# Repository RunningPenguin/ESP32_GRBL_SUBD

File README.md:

# ESP32_GRBL_SUBD

ESP32 GRBL adapter to SUB-D25

adapter to use the [ESP32 GRBL port](https://github.com/bdring/Grbl_Esp32) with
usual CNC machines, which are controlled via LPT (SUB-D25)

## PCB
PCBs [version 0.9.2](https://github.com/RunningPenguin/ESP32_GRBL_SUBD/tree/v0.9.2) could be
purchased using the gerber files contained in "gerbers/ESP32_GRBL_SUBD.zip" at JLCPCB

### TOP side

### BOT side

### received PCBs

### assembled PCB

### attached PCB

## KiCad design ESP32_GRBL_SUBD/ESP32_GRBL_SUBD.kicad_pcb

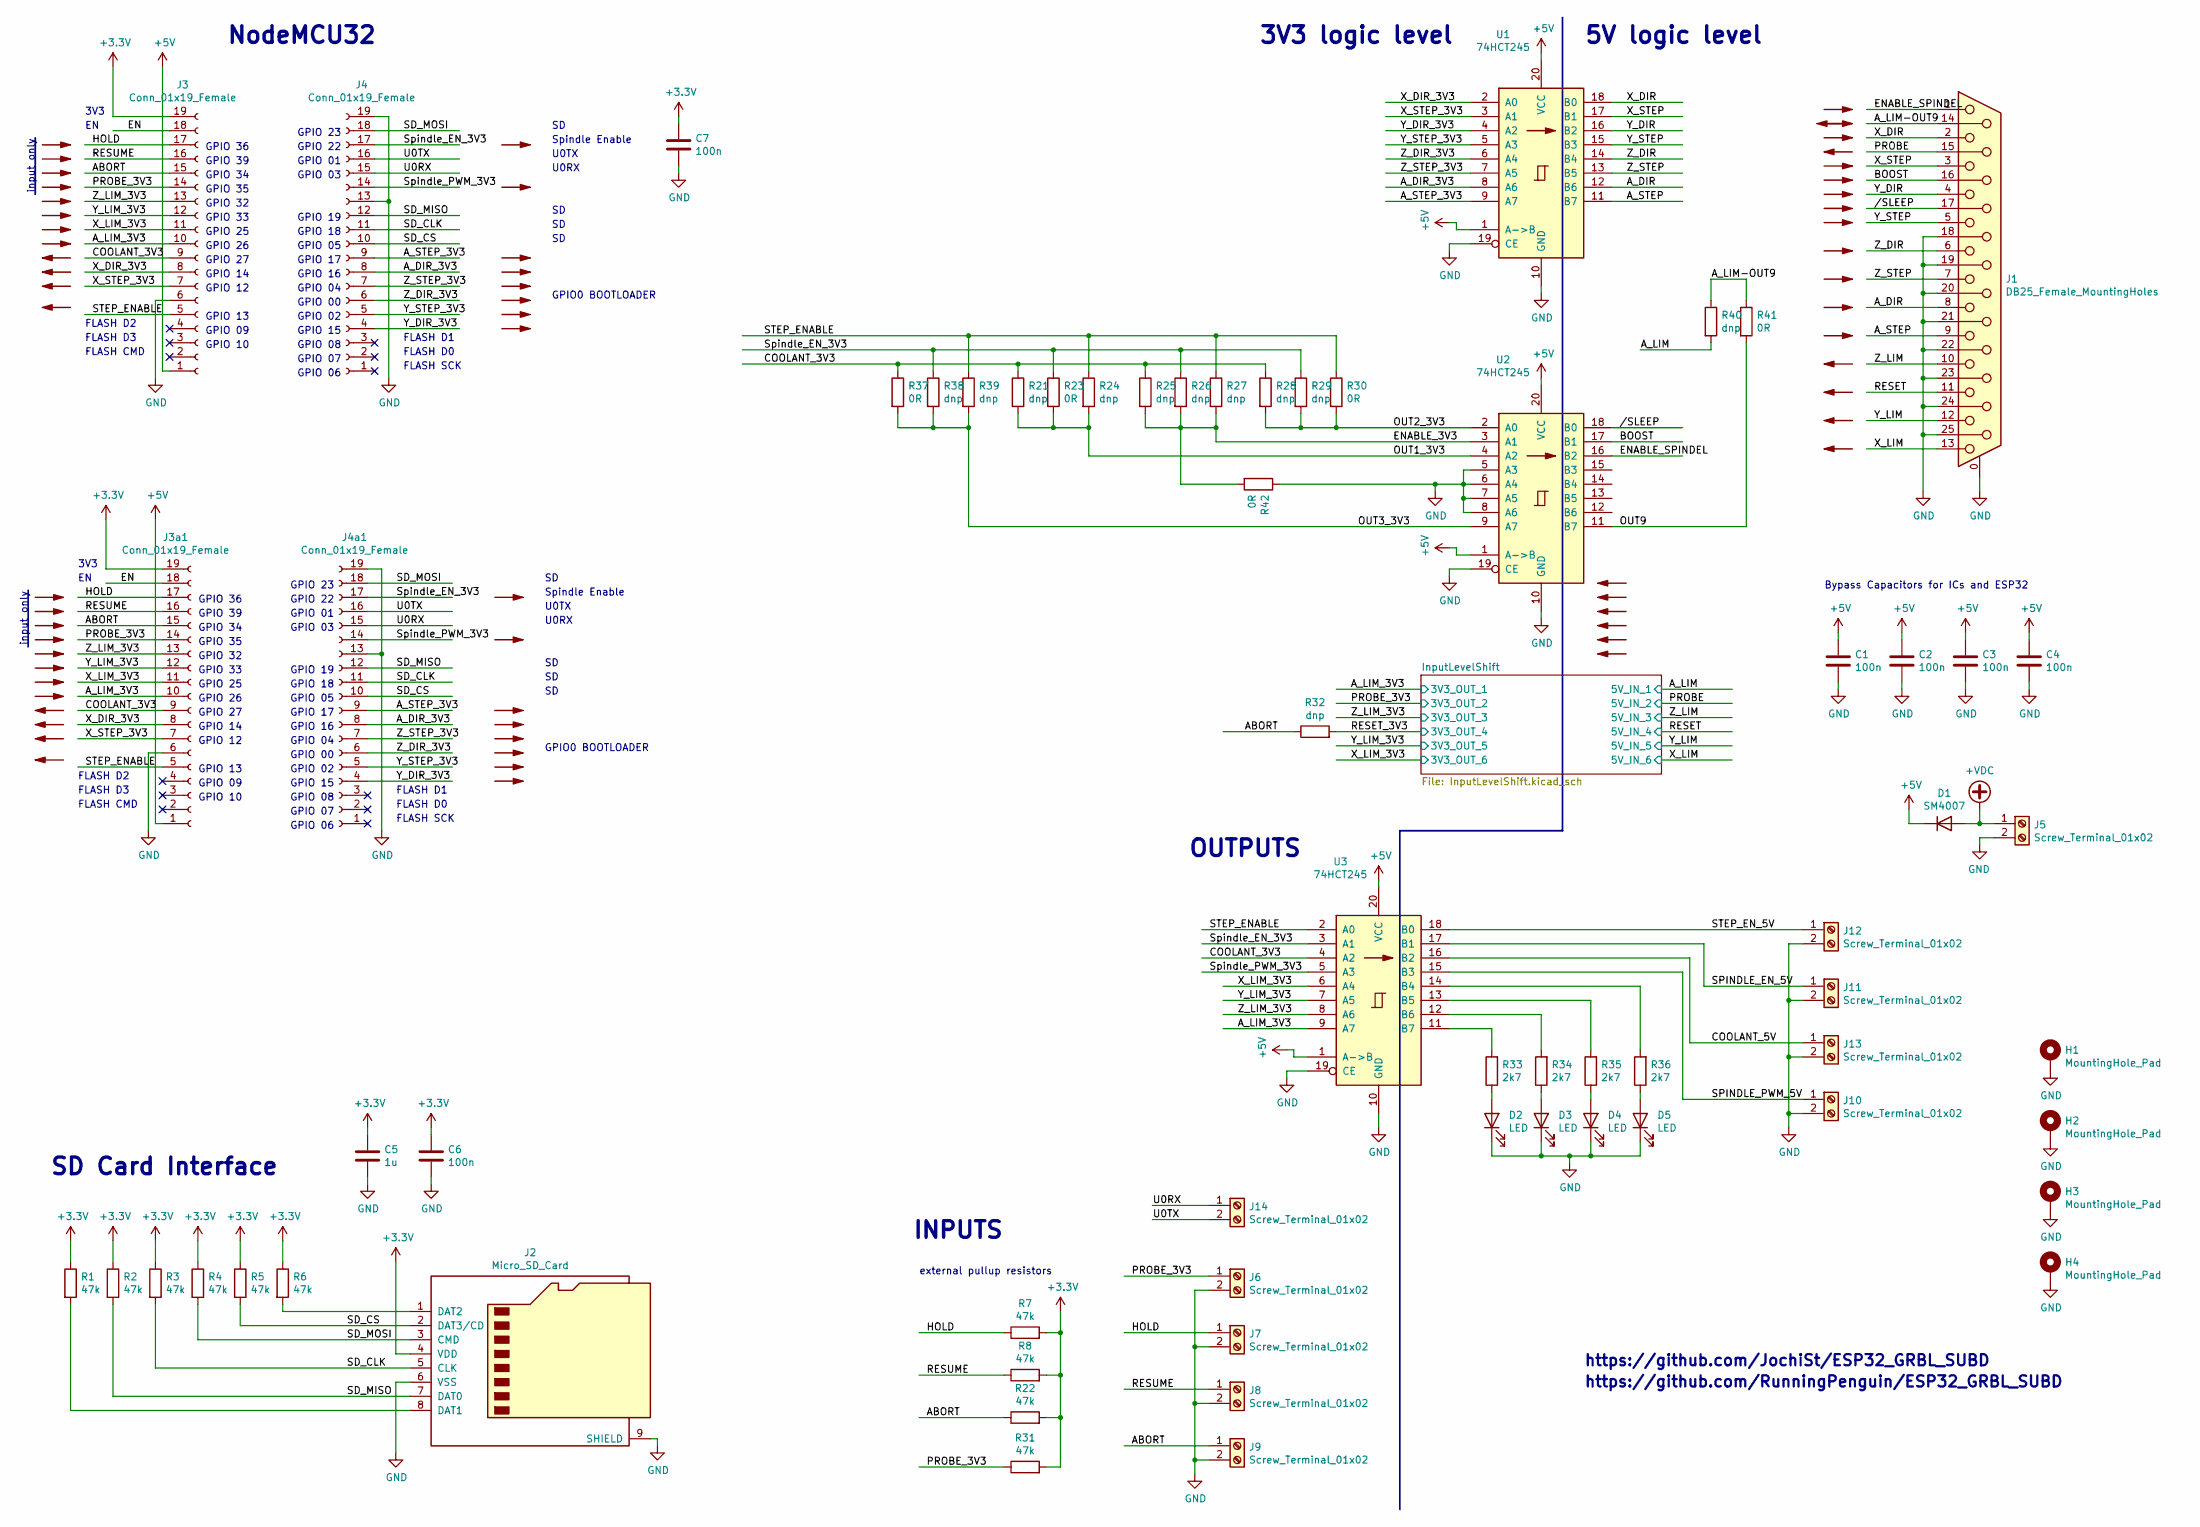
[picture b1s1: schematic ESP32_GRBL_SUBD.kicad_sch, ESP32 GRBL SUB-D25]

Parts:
C1, C2, C3, C4, C6, C7: 100n; C_0603_1608Metric
C5: 1u; C_0603_1608Metric
D1: SM4007; D_MELF
D2, D3, D4, D5: LED; LED_0603_1608Metric
H1, H2, H3, H4: MountingHole_Pad; MountingHole_3.2mm_M3_Pad_Via
J1: DB25_Female_MountingHoles; DSUB-25_Female_Horizontal_P2.77x2.84mm_EdgePinOffset7.70mm_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
J2: Micro_SD_Card; microSD_HC_Wuerth_693072010801
J3, J3a1, J4, J4a1: Conn_01x19_Female; PinSocket_1x19_P2.54mm_Vertical
J5, J6, J7, J8, J9, J10, J11, J12, J13, J14: Screw_Terminal_01x02; TerminalBlock_MetzConnect_Type055_RT01502HDWU_1x02_P5.00mm_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
R1, R2, R3, R4, R5, R6, R7, R8, R22, R31: 47k; R_0603_1608Metric
R21, R24, R25, R26, R27, R28, R29, R32, R38, R39, R40: dnp; R_0603_1608Metric
R23, R30, R37, R41, R42: 0R; R_0603_1608Metric
R33, R34, R35, R36: 2k7; R_0603_1608Metric
U1, U2, U3: 74HCT245; SO-20_12.8x7.5mm_P1.27mm

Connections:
+3V3: C5.1, C6.1, C7.1, J2.4 (VDD), J3.19, J3a1.19, R1.1, R2.1, R3.1, R4.1, R5.1, R6.1, R7.2, R8.2, R22.2, R31.2; also elsewhere on the board
+5V: C1.1, C2.1, C3.1, C4.1, D1.1 (K), J3.1, J3a1.1, U1.1 (A->B), U1.20 (VCC), U2.1 (A->B), U2.20 (VCC), U3.1 (A->B), U3.20 (VCC); also elsewhere on the board
+VDC: D1.2 (A), J5.1
/ABORT: J3.15, J3a1.15, J9.1, R22.1, R32.1
/A_DIR: J1.8, U1.12 (B6)
/A_DIR_3V3: J4.8, J4a1.8, U1.8 (A6)
/A_LIM: R40.2; also elsewhere on the board
/A_LIM-OUT9: J1.14, R40.1, R41.1
/A_LIM_3V3: J3.10, J3a1.10, U3.9 (A7); also elsewhere on the board
/A_STEP: J1.9, U1.11 (B7)
/A_STEP_3V3: J4.9, J4a1.9, U1.9 (A7)
/BOOST: J1.16, U2.17 (B1)
/COOLANT_3V3: J3.9, J3a1.9, R21.1, R25.1, R28.1, R37.1, U3.4 (A2)
/COOLANT_5V: J13.1, U3.16 (B2)
/EN: J3.18, J3a1.18
/ENABLE_3V3: R25.2, R26.2, R27.2, R42.2, U2.3 (A1)
/ENABLE_SPINDEL: J1.1, U2.16 (B2)
/HOLD: J3.17, J3a1.17, J7.1, R7.1
/OUT1_3V3: R21.2, R23.2, R24.2, U2.4 (A2)
/OUT2_3V3: R28.2, R29.2, R30.2, U2.2 (A0)
/OUT3_3V3: R37.2, R38.2, R39.2, U2.9 (A7)
/OUT9: R41.2, U2.11 (B7)
/PROBE: J1.15; also elsewhere on the board
/PROBE_3V3: J3.14, J3a1.14, J6.1, R31.1; also elsewhere on the board
/RESET: J1.11; also elsewhere on the board
/RESET_3V3: R32.2; also elsewhere on the board
/RESUME: J3.16, J3a1.16, J8.1, R8.1
/SD_CLK: J2.5 (CLK), J4.11, J4a1.11, R3.2
/SD_CS: J2.2 (DAT3/CD), J4.10, J4a1.10, R5.2
/SD_MISO: J2.7 (DAT0), J4.12, J4a1.12, R2.2
/SD_MOSI: J2.3 (CMD), J4.18, J4a1.18, R4.2
/SPINDLE_EN_5V: J11.1, U3.17 (B1)
/SPINDLE_PWM_5V: J10.1, U3.15 (B3)
/STEP_ENABLE: J3.5, J3a1.5, R24.1, R27.1, R30.1, R39.1, U3.2 (A0)
/STEP_EN_5V: J12.1, U3.18 (B0)
/Spindle_EN_3V3: J4.17, J4a1.17, R23.1, R26.1, R29.1, R38.1, U3.3 (A1)
/Spindle_PWM_3V3: J4.14, J4a1.14, U3.5 (A3)
/U0RX: J4.15, J4a1.15, J14.1
/U0TX: J4.16, J4a1.16, J14.2
/X_DIR: J1.2, U1.18 (B0)
/X_DIR_3V3: J3.8, J3a1.8, U1.2 (A0)
/X_LIM: J1.13; also elsewhere on the board
/X_LIM_3V3: J3.11, J3a1.11, U3.6 (A4); also elsewhere on the board
/X_STEP: J1.3, U1.17 (B1)
/X_STEP_3V3: J3.7, J3a1.7, U1.3 (A1)
/Y_DIR: J1.4, U1.16 (B2)
/Y_DIR_3V3: J4.4, J4a1.4, U1.4 (A2)
/Y_LIM: J1.12; also elsewhere on the board
/Y_LIM_3V3: J3.12, J3a1.12, U3.7 (A5); also elsewhere on the board
/Y_STEP: J1.5, U1.15 (B3)
/Y_STEP_3V3: J4.5, J4a1.5, U1.5 (A3)
/Z_DIR: J1.6, U1.14 (B4)
/Z_DIR_3V3: J4.6, J4a1.6, U1.6 (A4)
/Z_LIM: J1.10; also elsewhere on the board
/Z_LIM_3V3: J3.13, J3a1.13, U3.8 (A6); also elsewhere on the board
/Z_STEP: J1.7, U1.13 (B5)
/Z_STEP_3V3: J4.7, J4a1.7, U1.7 (A5)
//SLEEP: J1.17, U2.18 (B0)
GND: C1.2, C2.2, C3.2, C4.2, C5.2, C6.2, C7.2, D2.1 (K), D3.1 (K), D4.1 (K), D5.1 (K), H1.1, H2.1, H3.1, H4.1, J1.0 (PAD), J1.18, J1.19, J1.20, J1.21, J1.22, J1.23, J1.24, J1.25, J2.6 (VSS), J2.9 (SHIELD), J3.6, J3a1.6, J4.13, J4.19, J4a1.13, J4a1.19, J5.2, J6.2, J7.2, J8.2, J9.2, J10.2, J11.2, J12.2, J13.2, R42.1, U1.10 (GND), U1.19 (CE), U2.5 (A3), U2.6 (A4), U2.7 (A5), U2.8 (A6), U2.10 (GND), U2.19 (CE), U3.10 (GND), U3.19 (CE)
unnamed: D2.2 (A), R33.1
unnamed: D3.2 (A), R34.1
unnamed: D4.2 (A), R35.1
unnamed: D5.2 (A), R36.1
unnamed: J2.1 (DAT2), R6.2
unnamed: J2.8 (DAT1), R1.2
unnamed: R33.2, U3.11 (B7)
unnamed: R34.2, U3.12 (B6)
unnamed: R35.2, U3.13 (B5)
unnamed: R36.2, U3.14 (B4)

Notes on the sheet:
GPIO 03
GPIO 19
GPIO 01
GPIO 09
FLASH D0
GPIO 15
GPIO 27
GPIO 33
GPIO0 BOOTLOADER
GPIO 08
U0RX
FLASH CMD
GPIO 12
GPIO 32
GPIO 04
GPIO 02
3V3
GPIO 35
OUTPUTS
Spindle Enable
https://github.com/JochiSt/ESP32_GRBL_SUBD
GPIO 00
GPIO 23
GPIO 22
GPIO 25
Bypass Capacitors for ICs and ESP32
FLASH SCK
GPIO 34
GPIO 07
GPIO 10
5V logic level
input only
GPIO 36
FLASH D2
SD Card Interface
GPIO 26
GPIO 06
U0TX
GPIO 16
external pullup resistors

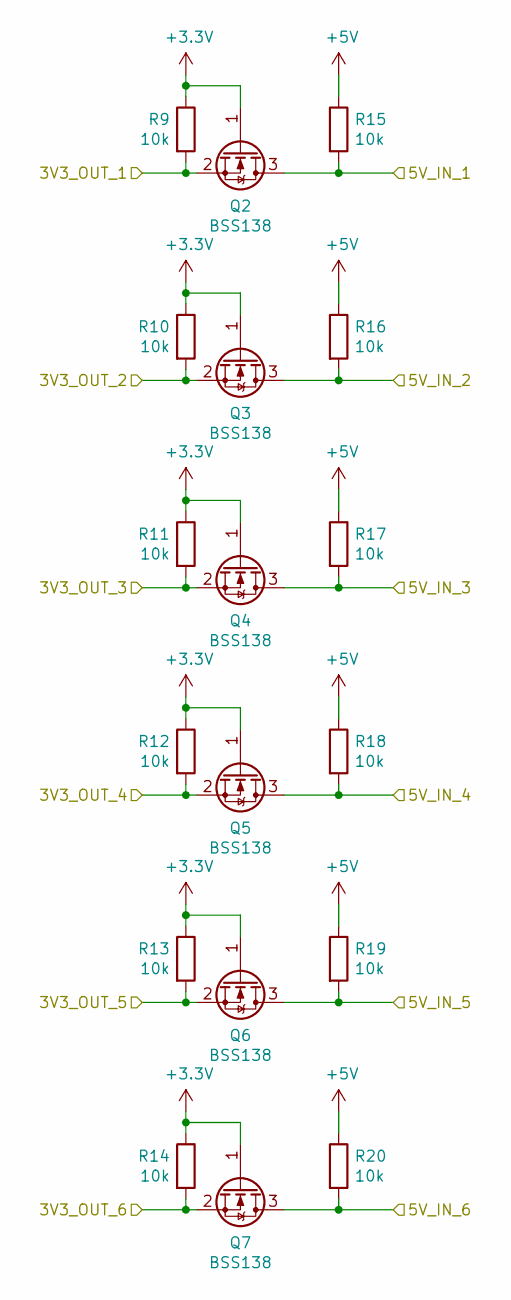
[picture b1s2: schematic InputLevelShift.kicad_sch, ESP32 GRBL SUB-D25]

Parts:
Q2, Q3, Q4, Q5, Q6, Q7: BSS138; SOT-23
R9, R10, R11, R12, R13, R14, R15, R16, R17, R18, R19, R20: 10k; R_0603_1608Metric

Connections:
+3V3: Q2.1 (G), Q3.1 (G), Q4.1 (G), Q5.1 (G), Q6.1 (G), Q7.1 (G), R9.1, R10.1, R11.1, R12.1, R13.1, R14.1; also elsewhere on the board
+5V: R15.1, R16.1, R17.1, R18.1, R19.1, R20.1; also elsewhere on the board
/A_LIM: Q2.3 (D), R15.2; also elsewhere on the board
/A_LIM_3V3: Q2.2 (S), R9.2; also elsewhere on the board
/PROBE: Q3.3 (D), R16.2; also elsewhere on the board
/PROBE_3V3: Q3.2 (S), R10.2; also elsewhere on the board
/RESET: Q5.3 (D), R18.2; also elsewhere on the board
/RESET_3V3: Q5.2 (S), R12.2; also elsewhere on the board
/X_LIM: Q7.3 (D), R20.2; also elsewhere on the board
/X_LIM_3V3: Q7.2 (S), R14.2; also elsewhere on the board
/Y_LIM: Q6.3 (D), R19.2; also elsewhere on the board
/Y_LIM_3V3: Q6.2 (S), R13.2; also elsewhere on the board
/Z_LIM: Q4.3 (D), R17.2; also elsewhere on the board
/Z_LIM_3V3: Q4.2 (S), R11.2; also elsewhere on the board

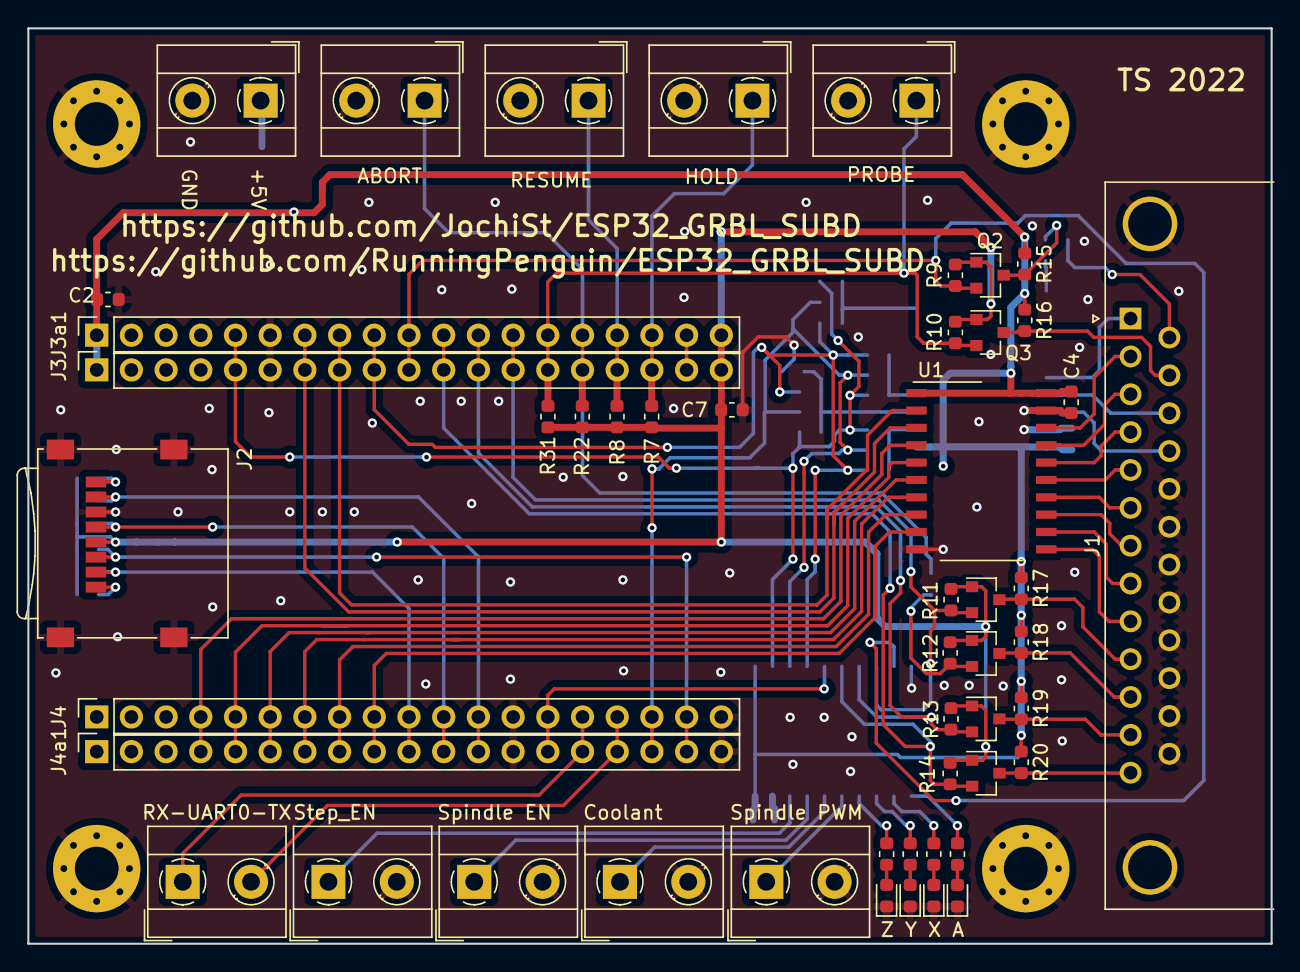
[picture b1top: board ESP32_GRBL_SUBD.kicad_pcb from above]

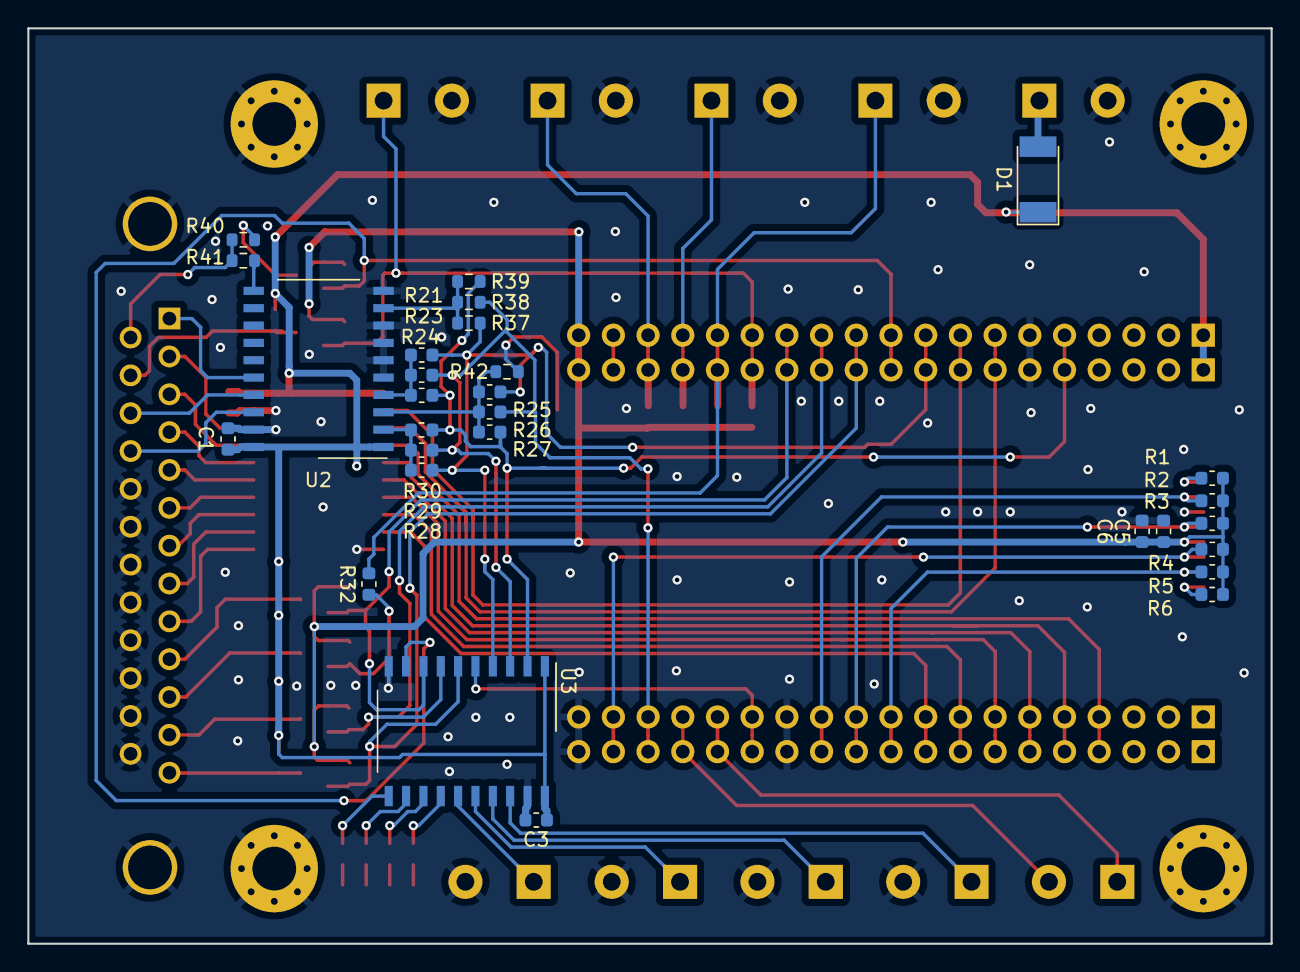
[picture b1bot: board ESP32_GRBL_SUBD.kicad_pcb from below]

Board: 2 copper layers, 91.0 x 67.0 mm, 83 parts (29 on the bottom side), 69 nets.

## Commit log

2022-12-18 D-Sub Pin 14 could be either a input or an output because my CNC milling machine uses this pin to switch on the coolant
2022-12-18 D-Sub Pin 14 could be either a input or an output because my CNC milling machine uses this pin to switch on the coolant. Untested PCB added
2022-12-18 One unused output pin resistor to GND added. The logic level converter shouldnt be floating
2022-12-19 mapped UART0 to screw header
2022-12-30 Configuration changed to L297/L298 Stepper driver from my CNC machine
2022-12-30 changed pictures to my actual PCBs. Changed Readme
2022-12-30 wired Axis a to screw terminals
2022-12-30 changed value of Resistor to match my actual soldered PCB
2022-12-30 rotate of the image
